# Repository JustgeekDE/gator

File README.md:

# Gator
Gator started as a small project to built a set of multipurpose, breadboard friendly TTL gates. It has since morphed into the endeavour to create a complete CPU built out of only discrete NPN transistors, resistors and capacitors.

## Errata
- The current instruction set is missing any way to read a memory address from a register. This makes pointers, array iterations and linked list impossible or at least very hard.

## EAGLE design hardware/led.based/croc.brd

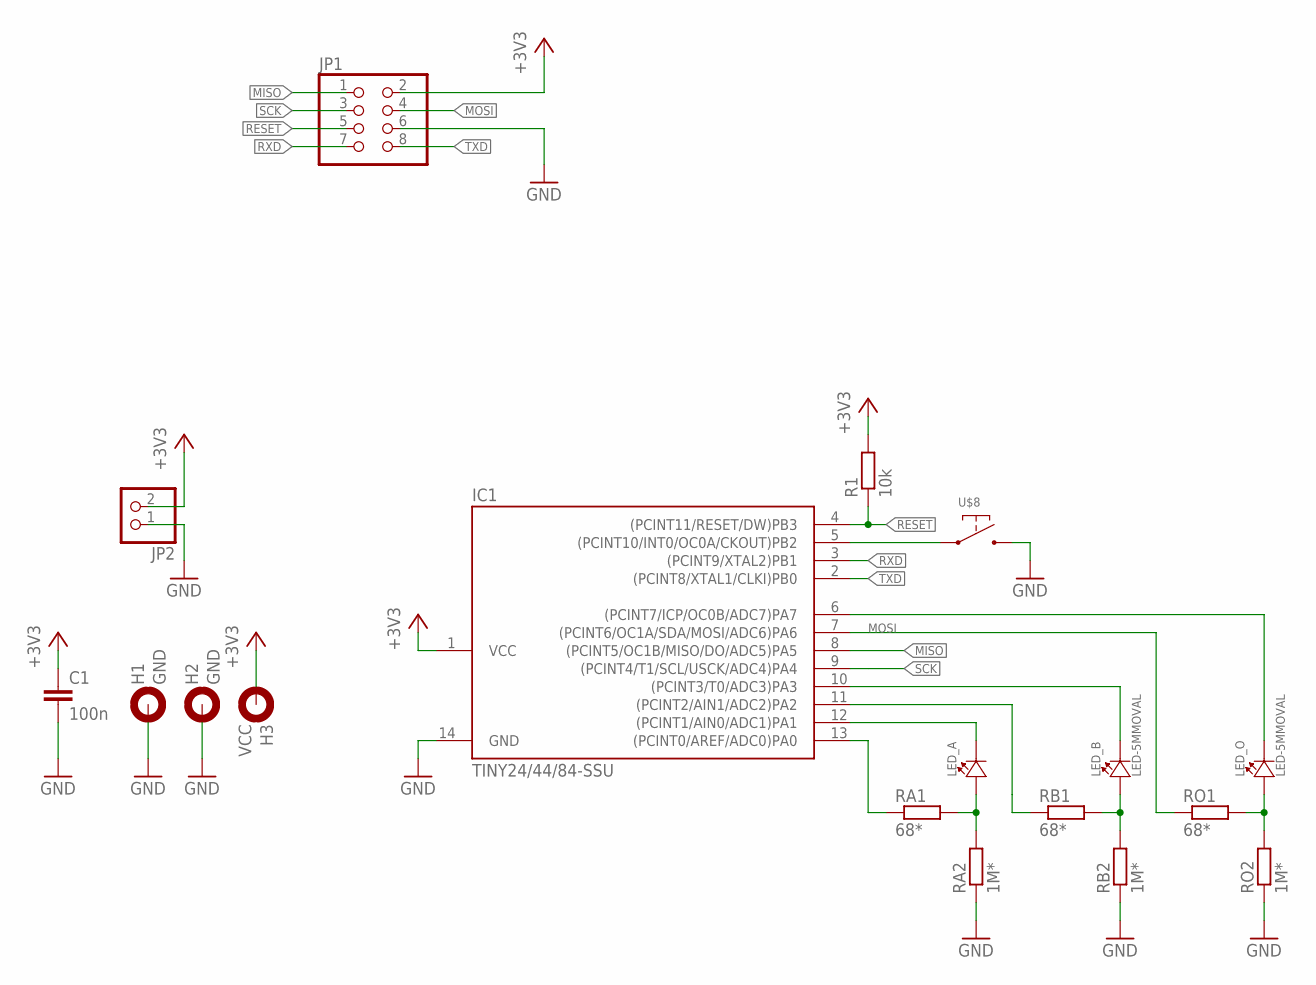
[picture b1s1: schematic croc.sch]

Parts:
C1: 100n; C0603; DIGIKEY 311-1343-1-ND
H1, H2: GND; 3,0-PAD
H3: VCC; 3,0-PAD
IC1: TINY24/44/84-SSU; SOIC14; DIGIKEY ATTINY84A-SSU-ND
JP1: PINHD-2X4/EDGE; 2X04/EDGE
JP2: PINHD-1X2; 1X02
LED_A: LED-5MMOVAL; LED-5MM-EDGE-OVAL
LED_B: LED-5MMOVAL; LED-5MM-EDGE-OVAL
LED_O: LED-5MMOVAL; LED-5MM-EDGE-OVAL
R1: 10k; R0603; DIGIKEY 311-10KGRCT-ND
RA1: 68*; R0603
RA2: 1M*; R0603
RB1: 68*; R0603
RB2: 1M*; R0603
RO1: 68*; R0603
RO2: 1M*; R0603
U$8: SWITCH-DEFAULT_OFF-NO_SILK; SWITCH-GENERIC-4_PIN-NO_SILK

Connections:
+3V3: C1.1, H3.B3,0, IC1.1 (VCC), JP1.2, JP2.2, R1.2
GND: C1.2, H1.B3,0, H2.B3,0, IC1.14 (GND), JP1.6, JP2.1, RA2.1, RB2.1, RO2.1, U$8.P$3, U$8.P$4
LED_A-C: IC1.12 ((PCINT1/AIN0/ADC1)PA1), LED_A.K (C)
LED_A-M: LED_A.A, RA1.2, RA2.2
LED_A-S: IC1.13 ((PCINT0/AREF/ADC0)PA0), RA1.1
LED_B-C: IC1.10 ((PCINT3/T0/ADC3)PA3), LED_B.K (C)
LED_B-M: LED_B.A, RB1.2, RB2.2
LED_B-S: IC1.11 ((PCINT2/AIN1/ADC2)PA2), RB1.1
LED_O-C: IC1.6 ((PCINT7/ICP/OC0B/ADC7)PA7), LED_O.K (C)
LED_O-M: LED_O.A, RO1.2, RO2.2
MISO: IC1.8 ((PCINT5/OC1B/MISO/DO/ADC5)PA5), JP1.1
MOSI: IC1.7 ((PCINT6/OC1A/SDA/MOSI/ADC6)PA6), JP1.4, RO1.1
unnamed: IC1.5 ((PCINT10/INT0/OC0A/CKOUT)PB2), U$8.P$1, U$8.P$2
RESET: IC1.4 ((PCINT11/RESET/DW)PB3), JP1.5, R1.1
RXD: IC1.3 ((PCINT9/XTAL2)PB1), JP1.7
SCK: IC1.9 ((PCINT4/T1/SCL/USCK/ADC4)PA4), JP1.3
TXD: IC1.2 ((PCINT8/XTAL1/CLKI)PB0), JP1.8

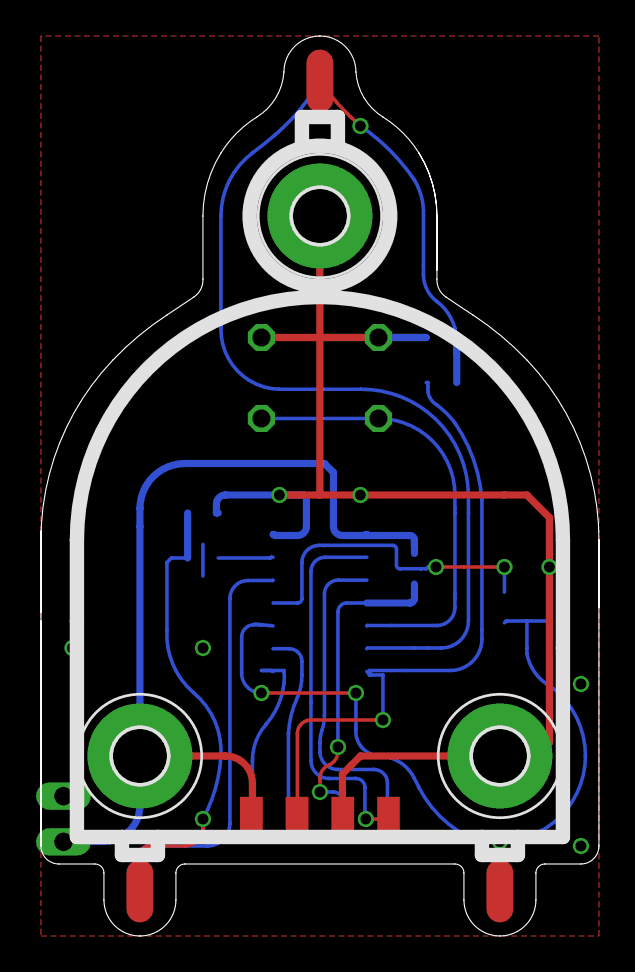
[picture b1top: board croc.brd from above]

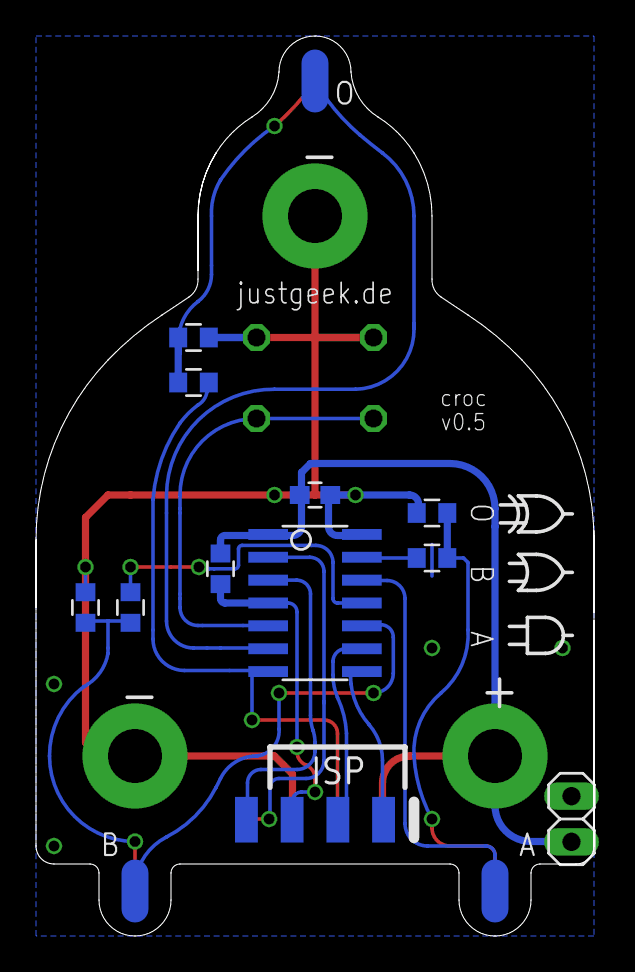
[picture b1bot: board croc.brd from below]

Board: 2 copper layers, 31.0 x 50.0 mm, 18 parts (11 on the bottom side), 17 nets.

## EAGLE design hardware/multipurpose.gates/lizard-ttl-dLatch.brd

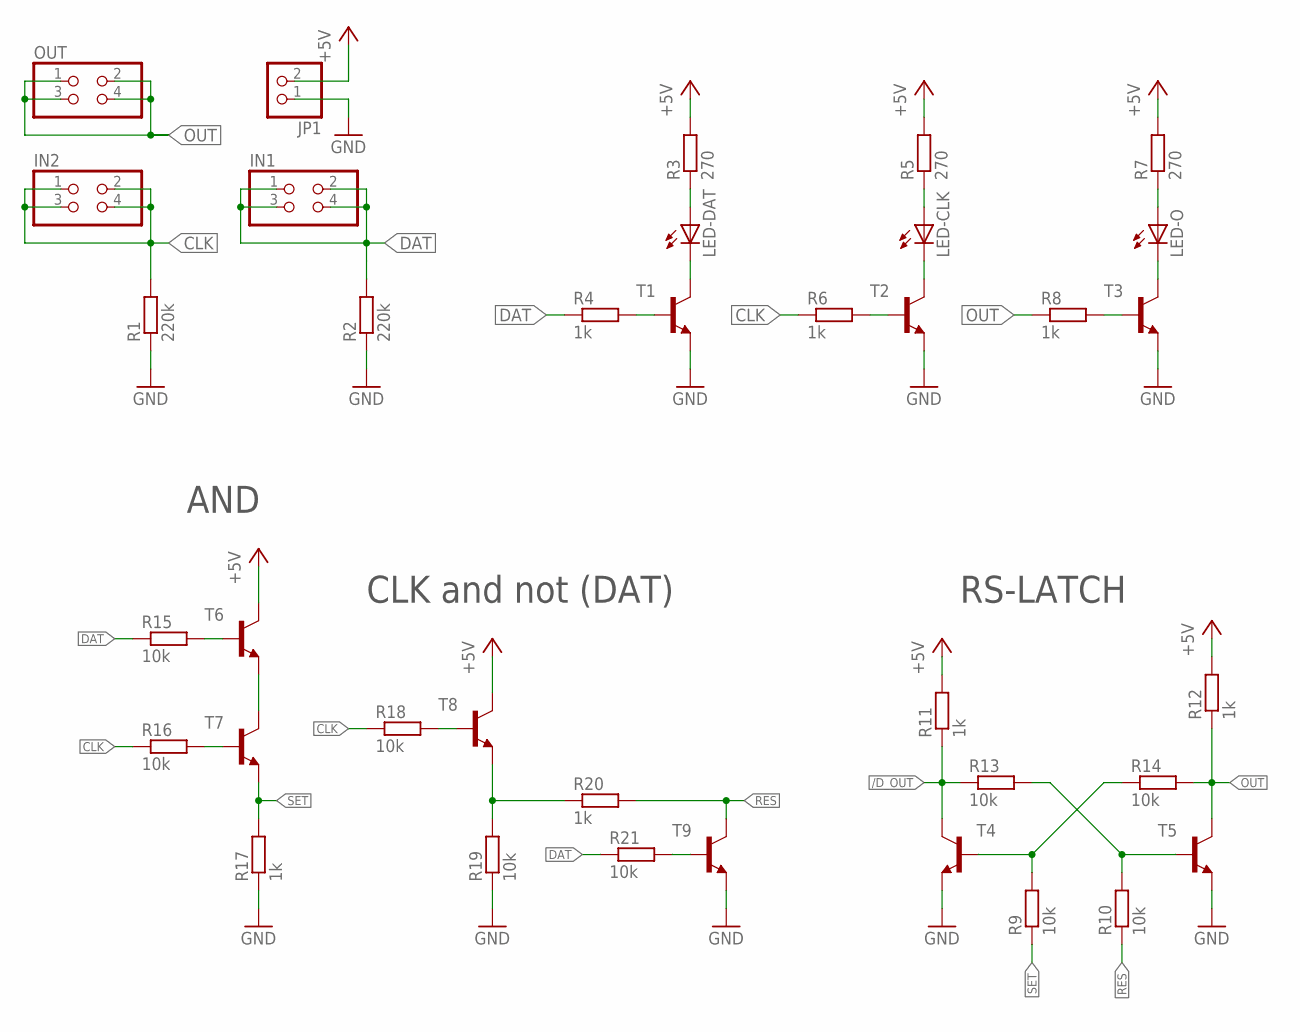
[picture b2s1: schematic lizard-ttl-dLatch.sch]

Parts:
IN1, IN2: PINHD-2X2/EDGE; 2X02/EDGE
JP1: PINHD-1X2; 1X02
LED-CLK: LEDCHIPLED_0603; CHIPLED_0603
LED-DAT: LEDCHIPLED_0603; CHIPLED_0603
LED-O: LEDCHIPLED_0603; CHIPLED_0603
OUT: PINHD-2X2/EDGE; 2X02/EDGE
R1, R2: 220k; R0603
R3, R5, R7: 270; R0603
R4, R6, R8, R11, R12, R17, R20: 1k; R0603
R9, R10, R13, R14, R15, R16, R18, R19, R21: 10k; R0603
T1, T2, T3, T4, T5, T6, T7, T8, T9: BC817-40-NPN-SOT23-BEC; SOT23-BEC

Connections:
+5V: JP1.2, R3.2, R5.2, R7.2, R11.2, R12.2, T6.C, T8.C
/D_OUT: R11.1, R13.1, T4.C
CLK: IN2.1, IN2.2, IN2.3, IN2.4, R1.2, R6.1, R16.1, R18.1
DAT: IN1.1, IN1.2, IN1.3, IN1.4, R2.2, R4.1, R15.1, R21.1
GND: JP1.1, R1.1, R2.1, R17.1, R19.1, T1.E, T2.E, T3.E, T4.E, T5.E, T9.E
unnamed: T6.E, T7.C
unnamed: R21.2, T9.B
unnamed: R4.2, T1.B
unnamed: LED-DAT.A, R3.1
unnamed: LED-DAT.C, T1.C
unnamed: R6.2, T2.B
unnamed: LED-CLK.A, R5.1
unnamed: LED-CLK.C, T2.C
unnamed: R8.2, T3.B
unnamed: LED-O.A, R7.1
unnamed: LED-O.C, T3.C
unnamed: R15.2, T6.B
unnamed: R16.2, T7.B
unnamed: R9.2, R14.1, T4.B
unnamed: R10.2, R13.2, T5.B
unnamed: R19.2, R20.1, T8.E
unnamed: R18.2, T8.B
OUT: OUT.1, OUT.2, OUT.3, OUT.4, R8.1, R12.1, R14.2, T5.C
RES: R10.1, R20.2, T9.C
SET: R9.1, R17.2, T7.E

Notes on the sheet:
RS-LATCH
AND
CLK and not (DAT)

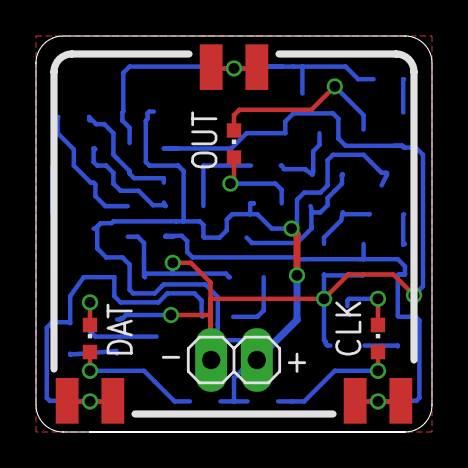
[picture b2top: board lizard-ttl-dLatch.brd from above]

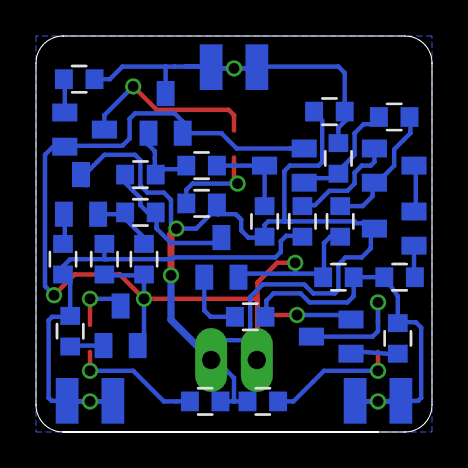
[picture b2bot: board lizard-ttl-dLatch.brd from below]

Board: 2 copper layers, 22.0 x 22.0 mm, 38 parts (30 on the bottom side), 25 nets.

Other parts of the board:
U$1: LOGO-JUSTGEEK-XS-MASK

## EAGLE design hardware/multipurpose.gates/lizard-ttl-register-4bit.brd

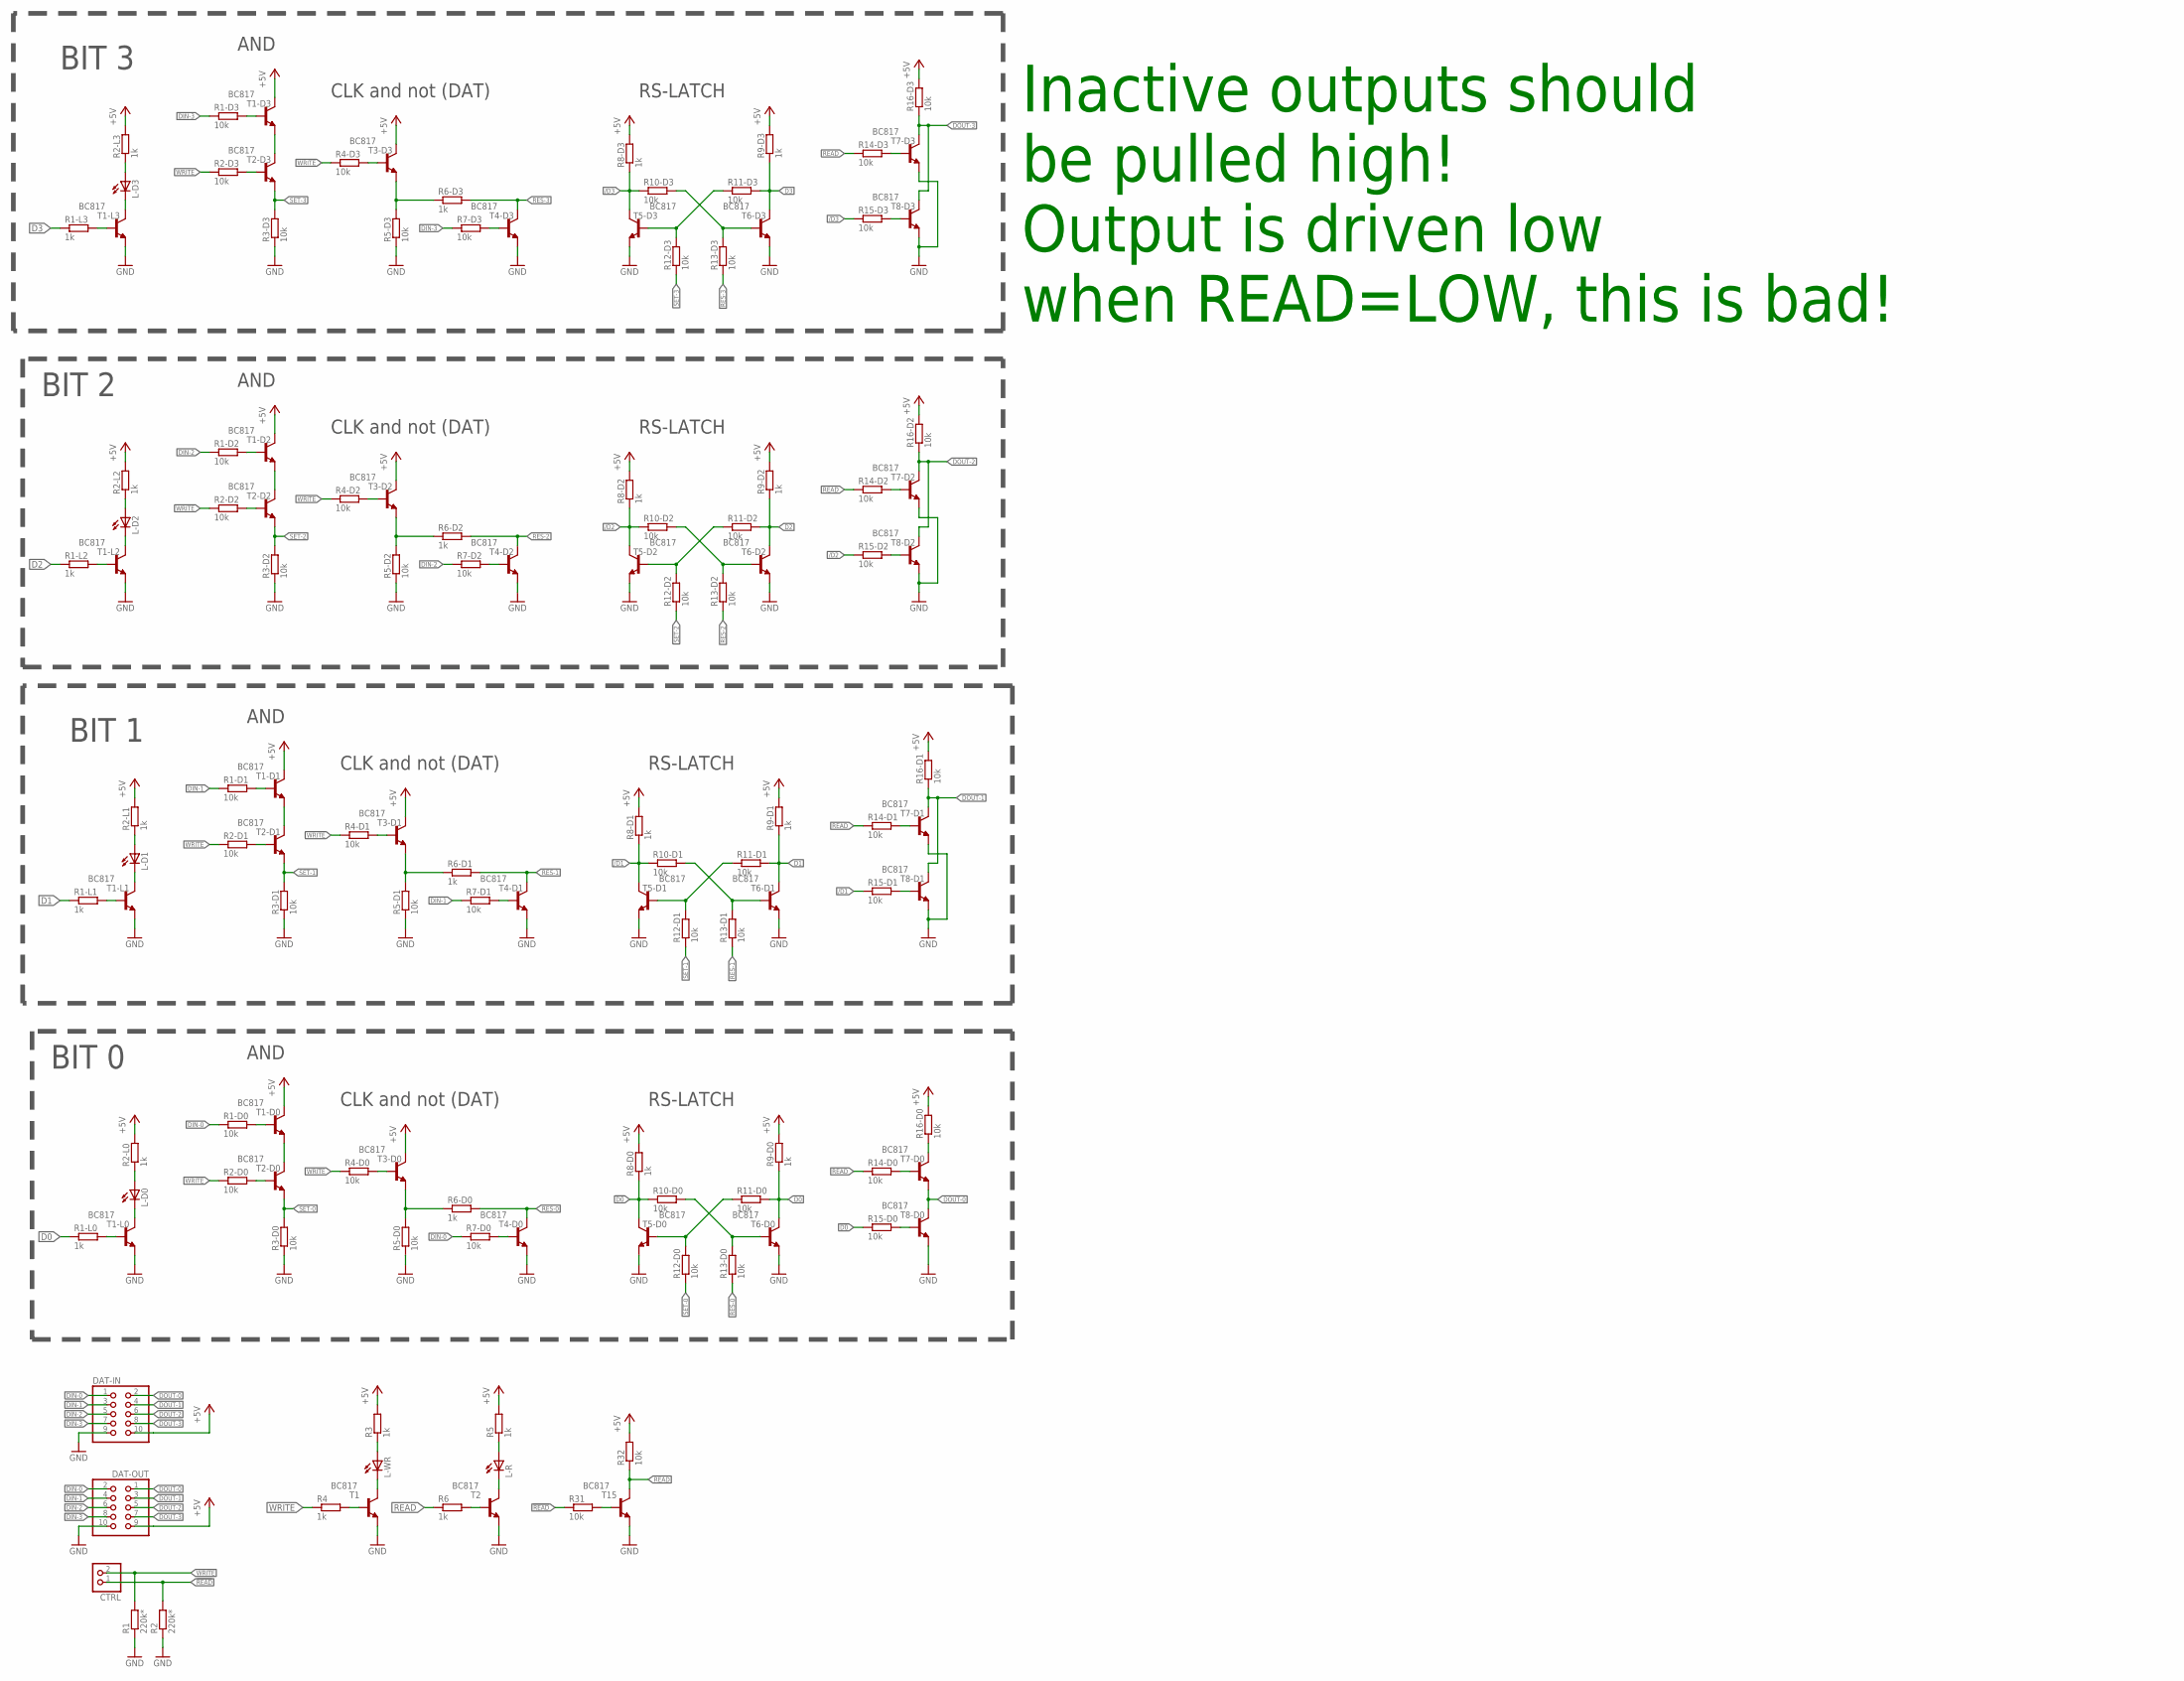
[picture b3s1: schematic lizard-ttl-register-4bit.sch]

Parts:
CTRL: PINHD-1X2; 1X02
DAT-IN: PINHD-2X5EDGE; 2X05/EDGE
DAT-OUT: PINHD-2X5EDGE; 2X05/EDGE
L-D0, L-D1, L-D2, L-D3: LEDCHIPLED_0603; CHIPLED_0603
L-R: LEDCHIPLED_0603; CHIPLED_0603
L-WR: LEDCHIPLED_0603; CHIPLED_0603
R1, R2: 220k*; R0603
R1-D0, R1-D1, R1-D2, R1-D3, R2-D0, R2-D1, R2-D2, R2-D3, R3-D0, R3-D1, R3-D2, R3-D3, R4-D0, R4-D1, R4-D2, R4-D3, R5-D0, R5-D1, R5-D2, R5-D3, R7-D0, R7-D1, R7-D2, R7-D3, R10-D0, R10-D1, R10-D2, R10-D3, R11-D0, R11-D1, R11-D2, R11-D3, R12-D0, R12-D1, R12-D2, R12-D3, R13-D0, R13-D1, R13-D2, R13-D3, R14-D0, R14-D1, R14-D2, R14-D3, R15-D0, R15-D1, R15-D2, R15-D3, R16-D0, R16-D1, R16-D2, R16-D3, R31, R32: 10k; R0603
R1-L0, R1-L1, R1-L2, R1-L3, R2-L0, R2-L1, R2-L2, R2-L3, R3, R4, R5, R6, R6-D0, R6-D1, R6-D2, R6-D3, R8-D0, R8-D1, R8-D2, R8-D3, R9-D0, R9-D1, R9-D2, R9-D3: 1k; R0603
T1, T1-D0, T1-D1, T1-D2, T1-D3, T1-L0, T1-L1, T1-L2, T1-L3, T2, T2-D0, T2-D1, T2-D2, T2-D3, T3-D0, T3-D1, T3-D2, T3-D3, T4-D0, T4-D1, T4-D2, T4-D3, T5-D0, T5-D1, T5-D2, T5-D3, T6-D0, T6-D1, T6-D2, T6-D3, T7-D0, T7-D1, T7-D2, T7-D3, T8-D0, T8-D1, T8-D2, T8-D3, T15: BC817; SOT23-BEC

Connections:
!D0: R8-D0.1, R10-D0.1, R15-D0.1, T5-D0.C
!READ: CTRL.1, R2.2, R31.1
+5V: DAT-IN.10, DAT-OUT.9, R2-L0.2, R2-L1.2, R2-L2.2, R2-L3.2, R3.2, R5.2, R8-D0.2, R8-D1.2, R8-D2.2, R8-D3.2, R9-D0.2, R9-D1.2, R9-D2.2, R9-D3.2, R16-D0.2, R16-D1.2, R16-D2.2, R16-D3.2, R32.2, T1-D0.C, T1-D1.C, T1-D2.C, T1-D3.C, T3-D0.C, T3-D1.C, T3-D2.C, T3-D3.C
/D1: R8-D1.1, R10-D1.1, R15-D1.1, T5-D1.C
/D2: R8-D2.1, R10-D2.1, R15-D2.1, T5-D2.C
/D3: R8-D3.1, R10-D3.1, R15-D3.1, T5-D3.C
D0: R1-L0.1, R9-D0.1, R11-D0.2, T6-D0.C
D1: R1-L1.1, R9-D1.1, R11-D1.2, T6-D1.C
D2: R1-L2.1, R9-D2.1, R11-D2.2, T6-D2.C
D3: R1-L3.1, R9-D3.1, R11-D3.2, T6-D3.C
DIN-0: DAT-IN.1, DAT-OUT.2, R1-D0.1, R7-D0.1
DIN-1: DAT-IN.3, DAT-OUT.4, R1-D1.1, R7-D1.1
DIN-2: DAT-IN.5, DAT-OUT.6, R1-D2.1, R7-D2.1
DIN-3: DAT-IN.7, DAT-OUT.8, R1-D3.1, R7-D3.1
DOUT-0: DAT-IN.2, DAT-OUT.1, T7-D0.E, T8-D0.C
DOUT-1: DAT-IN.4, DAT-OUT.3, R16-D1.1, T7-D1.C, T8-D1.C
DOUT-2: DAT-IN.6, DAT-OUT.5, R16-D2.1, T7-D2.C, T8-D2.C
DOUT-3: DAT-IN.8, DAT-OUT.7, R16-D3.1, T7-D3.C, T8-D3.C
GND: DAT-IN.9, DAT-OUT.10, R1.1, R2.1, R3-D0.1, R3-D1.1, R3-D2.1, R3-D3.1, R5-D0.1, R5-D1.1, R5-D2.1, R5-D3.1, T1.E, T1-L0.E, T1-L1.E, T1-L2.E, T1-L3.E, T2.E, T4-D0.E, T4-D1.E, T4-D2.E, T4-D3.E, T5-D0.E, T5-D1.E, T5-D2.E, T5-D3.E, T6-D0.E, T6-D1.E, T6-D2.E, T6-D3.E, T7-D1.E, T7-D2.E, T7-D3.E, T8-D0.E, T8-D1.E, T8-D2.E, T8-D3.E, T15.E
unnamed: T1-D0.E, T2-D0.C
unnamed: R7-D0.2, T4-D0.B
unnamed: R1-L1.2, T1-L1.B
unnamed: R4.2, T1.B
unnamed: L-WR.A, R3.1
unnamed: L-WR.C, T1.C
unnamed: R6.2, T2.B
unnamed: L-R.A, R5.1
unnamed: L-R.C, T2.C
unnamed: R1-L0.2, T1-L0.B
unnamed: L-D0.A, R2-L0.1
unnamed: L-D0.C, T1-L0.C
unnamed: L-D1.A, R2-L1.1
unnamed: R1-D0.2, T1-D0.B
unnamed: R2-D0.2, T2-D0.B
unnamed: R11-D0.1, R12-D0.2, T5-D0.B
unnamed: R10-D0.2, R13-D0.2, T6-D0.B
unnamed: L-D1.C, T1-L1.C
unnamed: R5-D0.2, R6-D0.1, T3-D0.E
unnamed: R1-D1.2, T1-D1.B
unnamed: R2-D1.2, T2-D1.B
unnamed: R5-D1.2, R6-D1.1, T3-D1.E
unnamed: R4-D0.2, T3-D0.B
unnamed: R4-D1.2, T3-D1.B
unnamed: T1-D1.E, T2-D1.C
unnamed: R7-D1.2, T4-D1.B
unnamed: R14-D0.2, T7-D0.B
unnamed: R15-D0.2, T8-D0.B
unnamed: R31.2, T15.B
unnamed: R11-D1.1, R12-D1.2, T5-D1.B
unnamed: R10-D1.2, R13-D1.2, T6-D1.B
unnamed: R14-D1.2, T7-D1.B
unnamed: R15-D1.2, T8-D1.B
unnamed: R1-L2.2, T1-L2.B
unnamed: L-D2.A, R2-L2.1
unnamed: L-D2.C, T1-L2.C
unnamed: R1-D2.2, T1-D2.B
unnamed: R2-D2.2, T2-D2.B
unnamed: R5-D2.2, R6-D2.1, T3-D2.E
unnamed: R4-D2.2, T3-D2.B
unnamed: T1-D2.E, T2-D2.C
unnamed: R7-D2.2, T4-D2.B
unnamed: R11-D2.1, R12-D2.2, T5-D2.B
unnamed: R10-D2.2, R13-D2.2, T6-D2.B
unnamed: R14-D2.2, T7-D2.B
unnamed: R15-D2.2, T8-D2.B
unnamed: R1-L3.2, T1-L3.B
unnamed: L-D3.A, R2-L3.1
unnamed: L-D3.C, T1-L3.C
unnamed: R1-D3.2, T1-D3.B
unnamed: R2-D3.2, T2-D3.B
unnamed: R5-D3.2, R6-D3.1, T3-D3.E
unnamed: R4-D3.2, T3-D3.B
unnamed: T1-D3.E, T2-D3.C
unnamed: R7-D3.2, T4-D3.B
unnamed: R11-D3.1, R12-D3.2, T5-D3.B
unnamed: R10-D3.2, R13-D3.2, T6-D3.B
unnamed: R14-D3.2, T7-D3.B
unnamed: R15-D3.2, T8-D3.B
unnamed: R16-D0.1, T7-D0.C
READ: R6.1, R14-D0.1, R14-D1.1, R14-D2.1, R14-D3.1, R32.1, T15.C
RES-0: R6-D0.2, R13-D0.1, T4-D0.C
RES-1: R6-D1.2, R13-D1.1, T4-D1.C
RES-2: R6-D2.2, R13-D2.1, T4-D2.C
RES-3: R6-D3.2, R13-D3.1, T4-D3.C
SET-0: R3-D0.2, R12-D0.1, T2-D0.E
SET-1: R3-D1.2, R12-D1.1, T2-D1.E
SET-2: R3-D2.2, R12-D2.1, T2-D2.E
SET-3: R3-D3.2, R12-D3.1, T2-D3.E
WRITE: CTRL.2, R1.2, R2-D0.1, R2-D1.1, R2-D2.1, R2-D3.1, R4.1, R4-D0.1, R4-D1.1, R4-D2.1, R4-D3.1

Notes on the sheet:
RS-LATCH
AND
CLK and not (DAT)
BIT 0
BIT 1
BIT 2
BIT 3
Inactive outputs should be pulled high! Output is driven low when READ=LOW, this is bad!

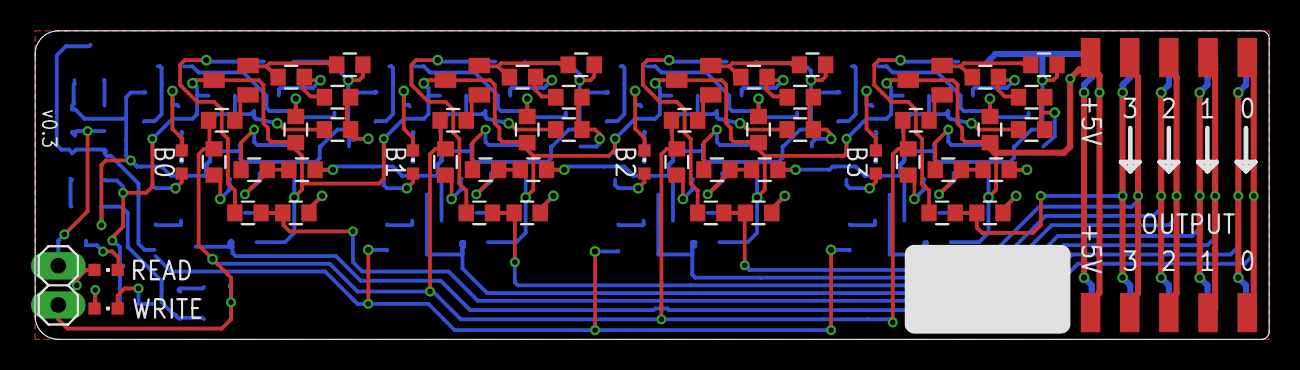
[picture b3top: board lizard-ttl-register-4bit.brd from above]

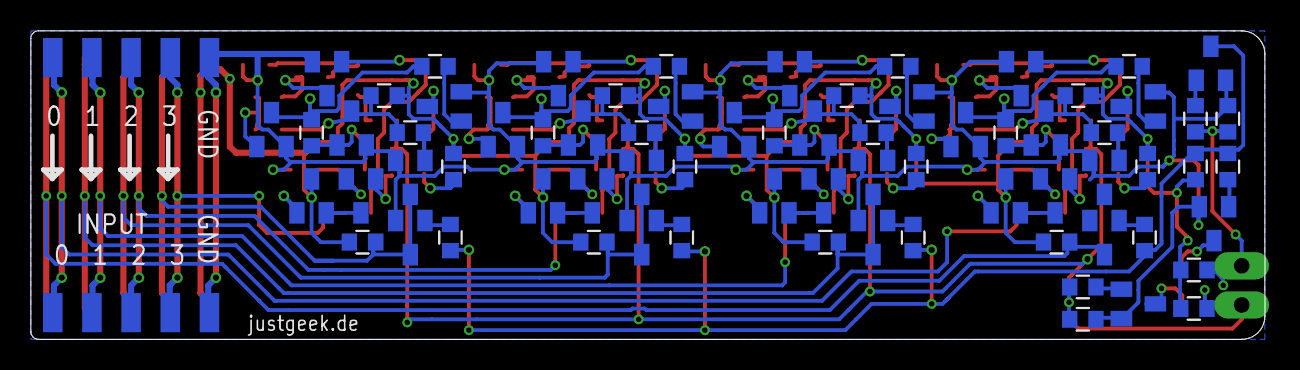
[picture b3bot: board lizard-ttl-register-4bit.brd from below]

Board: 2 copper layers, 80.0 x 20.0 mm, 129 parts (72 on the bottom side), 89 nets.

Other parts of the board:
U$1: LOGO-JUSTGEEK-XS-MASK

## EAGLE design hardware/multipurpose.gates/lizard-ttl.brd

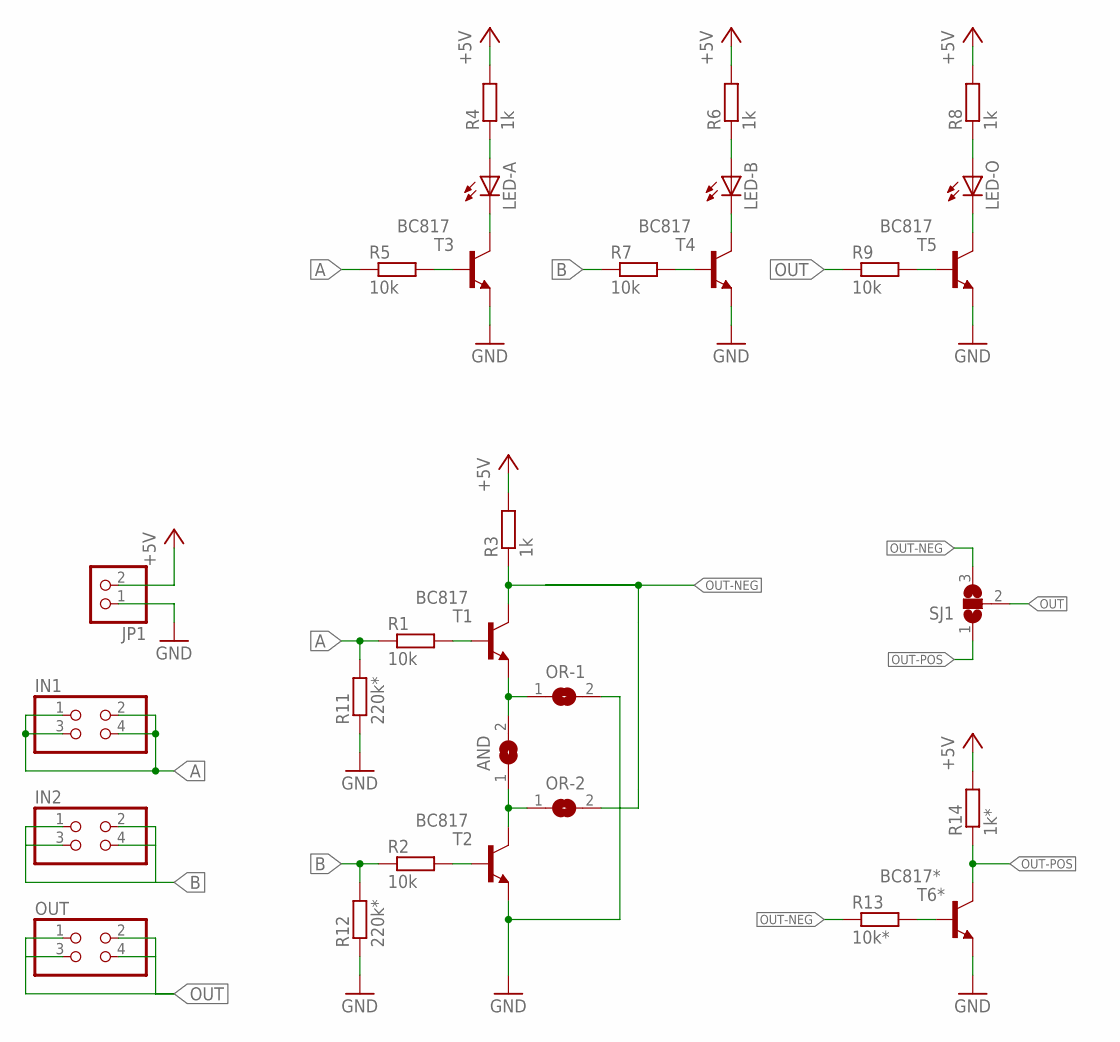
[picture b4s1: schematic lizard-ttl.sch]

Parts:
AND: SJ
IN1, IN2: PINHD-2X2/EDGE; 2X02/EDGE
JP1: PINHD-1X2; 1X02
LED-A: LEDCHIPLED_0603; CHIPLED_0603
LED-B: LEDCHIPLED_0603; CHIPLED_0603
LED-O: LEDCHIPLED_0603; CHIPLED_0603
OR-1, OR-2: SJ
OUT: PINHD-2X2/EDGE; 2X02/EDGE
R1, R2, R5, R7, R9: 10k; R0603
R3, R4, R6, R8: 1k; R0603
R11, R12: 220k*; R0603
R13: 10k*; R0603
R14: 1k*; R0603
SJ1: SJ2W; SJ_2
T1, T2, T3, T4, T5: BC817; SOT23-BEC
T6*: BC817*; SOT23-BEC

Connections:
+5V: JP1.2, R3.2, R4.2, R6.2, R8.2, R14.2
A: IN1.1, IN1.2, IN1.3, IN1.4, R1.1, R5.1, R11.2
B: IN2.1, IN2.2, IN2.3, IN2.4, R2.1, R7.1, R12.2
GND: JP1.1, OR-1.2, R11.1, R12.1, T2.E, T3.E, T4.E, T5.E, T6*.E
unnamed: R1.2, T1.B
unnamed: AND.2, OR-1.1, T1.E
unnamed: R2.2, T2.B
unnamed: R5.2, T3.B
unnamed: LED-A.A, R4.1
unnamed: LED-A.C, T3.C
unnamed: R7.2, T4.B
unnamed: LED-B.A, R6.1
unnamed: LED-B.C, T4.C
unnamed: R9.2, T5.B
unnamed: LED-O.A, R8.1
unnamed: LED-O.C, T5.C
unnamed: AND.1, OR-2.1, T2.C
unnamed: R13.2, T6*.B
OUT: OUT.1, OUT.2, OUT.3, OUT.4, R9.1, SJ1.2
OUT-NEG: OR-2.2, R3.1, R13.1, SJ1.3, T1.C
OUT-POS: R14.1, SJ1.1, T6*.C

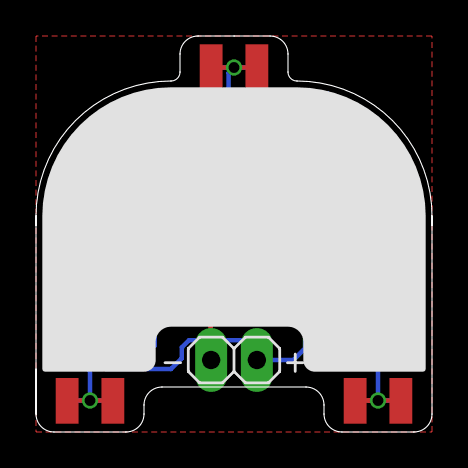
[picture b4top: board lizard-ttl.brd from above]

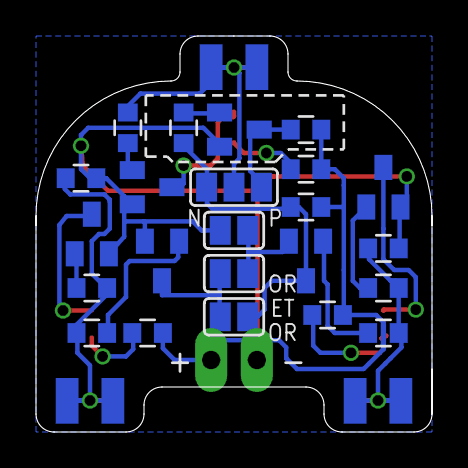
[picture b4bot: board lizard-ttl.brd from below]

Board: 2 copper layers, 22.0 x 22.0 mm, 32 parts (23 on the bottom side), 21 nets.

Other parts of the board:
U$1, U$2: LOGO-JUSTGEEK-XS-MASK

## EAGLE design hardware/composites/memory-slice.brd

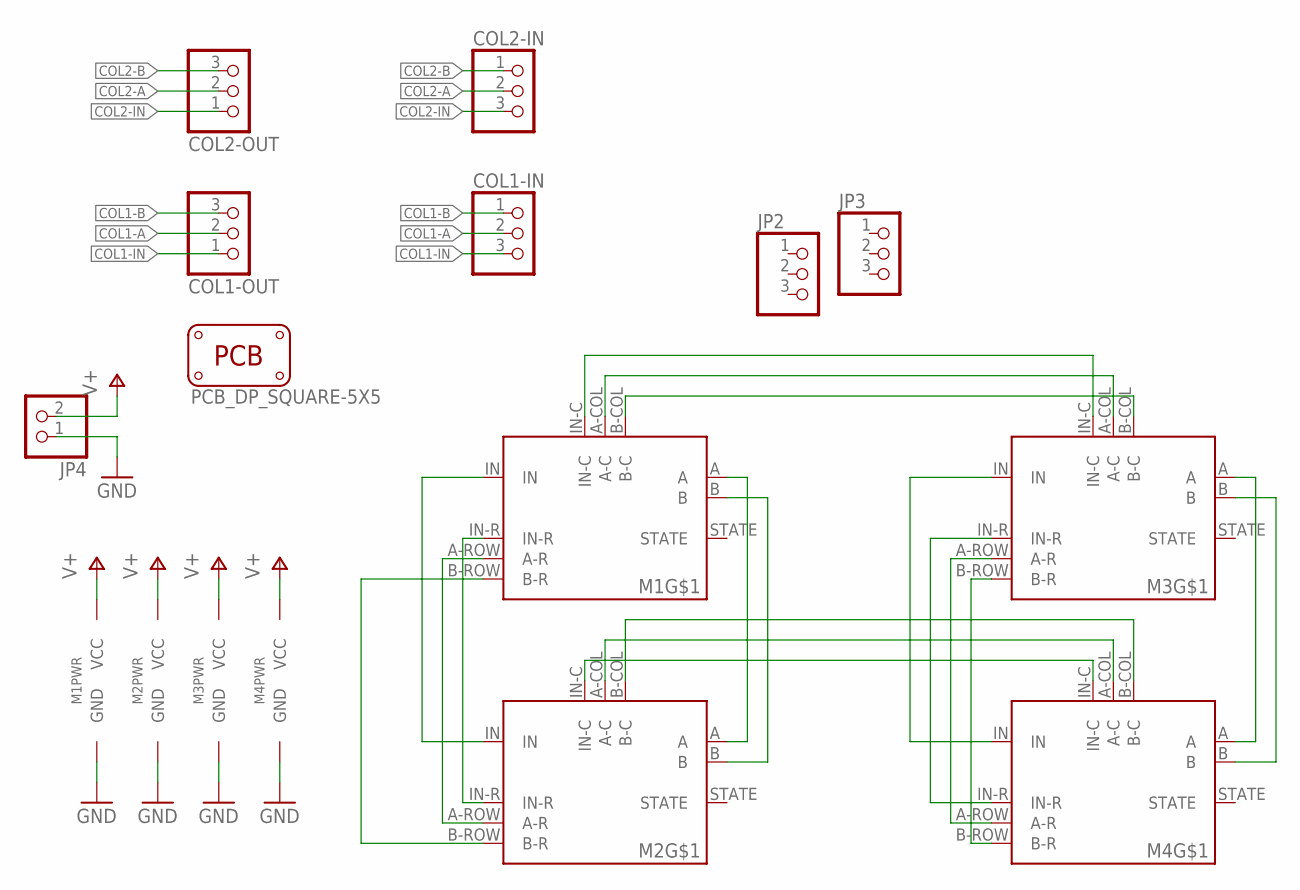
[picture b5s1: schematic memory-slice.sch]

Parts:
COL1-IN, COL1-OUT, COL2-IN, COL2-OUT: PINHD-1X3/90; 1X03/90
JP2, JP3: PINHD-1X3/90; 1X03/90
JP4: PINHD-1X2; 1X02
M1, M2, M3, M4: MEMORY-1BIT-CELL
PCB1: PCB_DP_SQUARE-5X5; DP5050_V1

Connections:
COL1-A: COL1-IN.2, COL1-OUT.2, M1.A-COL (A-C), M3.A-COL (A-C)
COL1-B: COL1-IN.1, COL1-OUT.3, M1.B-COL (B-C), M3.B-COL (B-C)
COL1-IN: COL1-IN.3, COL1-OUT.1, M1.IN-C, M3.IN-C
COL2-A: COL2-IN.2, COL2-OUT.2, M2.A-COL (A-C), M4.A-COL (A-C)
COL2-B: COL2-IN.1, COL2-OUT.3, M2.B-COL (B-C), M4.B-COL (B-C)
COL2-IN: COL2-IN.3, COL2-OUT.1, M2.IN-C, M4.IN-C
GND: JP4.1, M1.GND, M2.GND, M3.GND, M4.GND
unnamed: M1.IN, M2.IN
unnamed: M3.IN, M4.IN
unnamed: M3.B-ROW (B-R), M4.B-ROW (B-R)
unnamed: M3.A-ROW (A-R), M4.A-ROW (A-R)
unnamed: M3.IN-R, M4.IN-R
unnamed: M3.A, M4.A
unnamed: M3.B, M4.B
unnamed: M1.IN-R, M2.IN-R
unnamed: M1.A, M2.A
unnamed: M1.B, M2.B
unnamed: M1.A-ROW (A-R), M2.A-ROW (A-R)
unnamed: M1.B-ROW (B-R), M2.B-ROW (B-R)
V+: JP4.2, M1.VCC, M2.VCC, M3.VCC, M4.VCC

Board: 2 copper layers, 12 parts (0 on the bottom side), 20 nets, no tracks yet.
